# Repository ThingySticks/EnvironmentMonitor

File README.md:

# Environment Monitor ThingySticks

Particle Photon or Electron based board to measure Humidity, Temperature, Light level and pressure.

* Compaible with Particle Power Shield to allow completly wireless monitoring.
* Compaible with Particle Asset Sheild to allow location information to be included with sensor data.
* Works with Photon or Electron.

## V2:

* Temperature, Humidity (HTU21D)
* Pressure (BMP180)
* Light (TEMT6000)
* Uses a Particle Photon or Electron
* Can piggyback onto Particle Asset Tracker and other ThingySticks prototype PCBs

Available on Tindie: https://www.tindie.com/products/ThingySticks/environment-sensor-for-the-photon-or-electron/

## V3:

Uses a BME680 - These are currently very hard (i.e. impossible) to get hold of. They were expected to be sold over a year ago, hence V3 of the monitor is on-hold.

## V4:

* Total Volatile Organic Compounds (TVOC) (CCS811)
* Equivelant CO2 (CCS811)
* Temperature, Humidity and Pressure (BME280)
* Light (TEMT6000)
* Uses a Particle Photon or Electron
* Can piggyback onto Particle Asset Tracker and other ThingySticks prototype PCBs

Available on Tindie: https://www.tindie.com/products/ThingySticks/air-quality-sensor-bme280ccs811-thingystick/

Build Files
-----------

Files used by the CI server to automate Eagle as part of a build process.

Clean.bat - As it says, pre build clean.
Build.bat - The build tasks (Generate images of the schematic, PCB top, bottom, all and measurements layers).
Distribute.bat - Copy the images to the appropriate places (S3....)

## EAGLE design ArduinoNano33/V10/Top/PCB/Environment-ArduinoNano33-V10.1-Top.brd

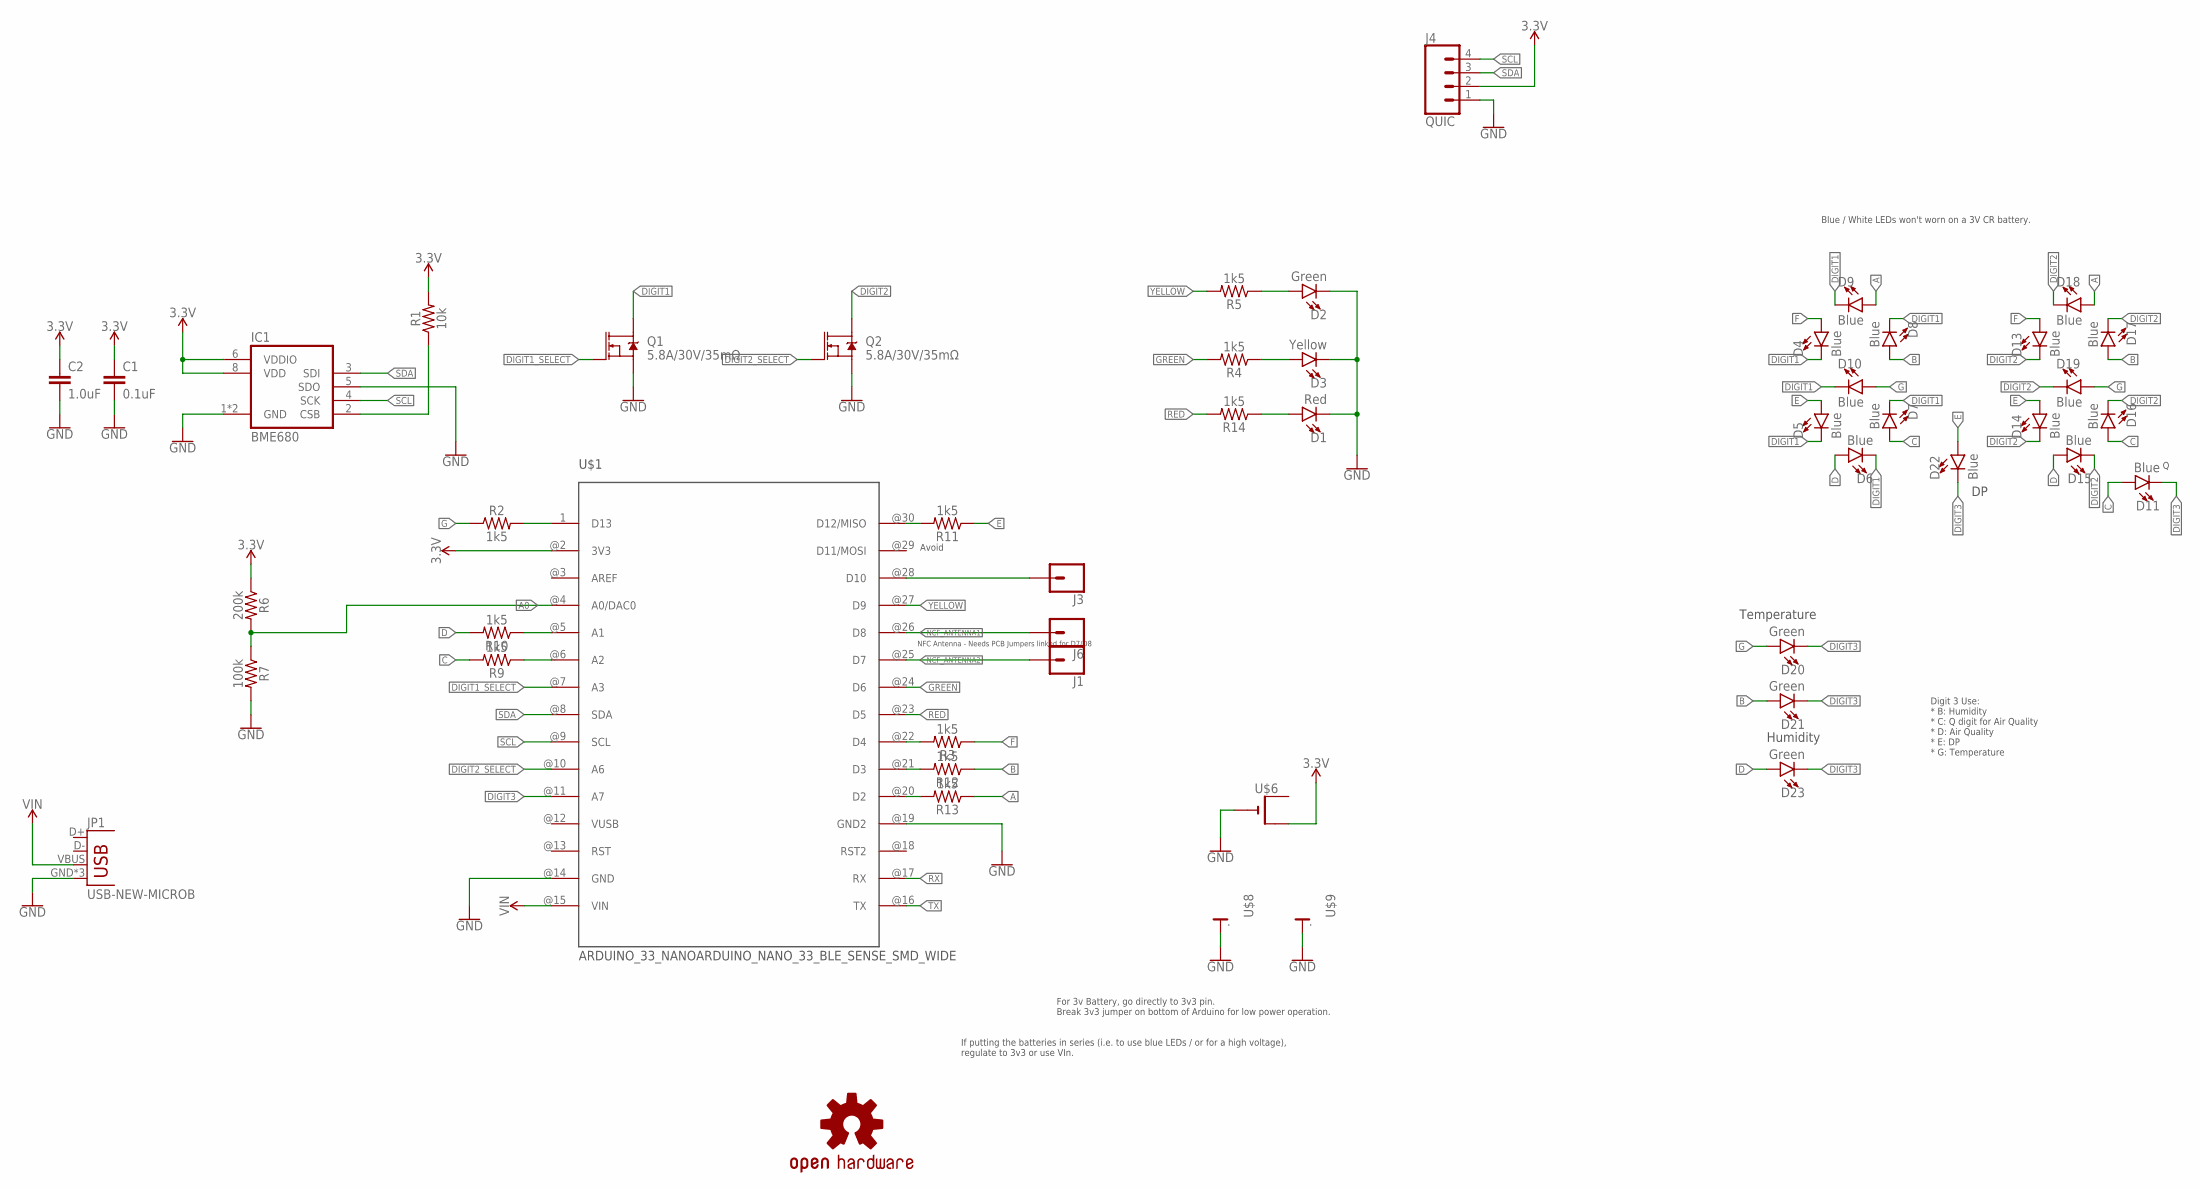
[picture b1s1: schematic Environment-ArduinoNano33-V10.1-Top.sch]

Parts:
C1: 0.1uF; 0805
C2: 1.0uF; 0805
D1: Red; LED-1206
D2, D20, D21, D23: Green; LED-1206
D3: Yellow; LED-1206
D4, D5, D6, D7, D8, D9, D10, D11, D13, D14, D15, D16, D17, D18, D19, D22: Blue; LED-1206
IC1: BME680
J1, J3, J6: CONN_01; 1X01
J4: QUIC; JST04_1MM_RA
JP1: USB-NEW-MICROB; USB-MICROB
LOGO1: OSHW-LOGOM; OSHW-LOGO-M
Q1, Q2: 5.8A/30V/35mΩ; SOT23-3
R1: 10k; 0805
R2, R3, R4, R5, R9, R10, R11, R12, R13, R14: 1k5; 0805
R6: 200k; 0805
R7: 100k; 0805
U$1: ARDUINO_33_NANOARDUINO_NANO_33_BLE_SENSE_SMD_WIDE; ARDUINO_NANO_33_SMD_WIDER_PADS
U$6: CR2032SMT; CR2032-SMD
U$8, U$9: CR2032-SPLIT-PCBCR2032-NEGATIVE; CR2032-SMD-NEGATIVE-TERMINAL

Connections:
3.3V: C1.1, C2.1, IC1.6 (VDDIO), IC1.8 (VDD), J4.2, R1.2, R6.1, U$1.@2 (3V3), U$6.+$2 (+1)
A: D9.A, D18.A, R13.1
A0: R6.2, R7.1, U$1.@4 (A0/DAC0)
B: D8.A, D17.A, D21.A, R12.1
C: D7.A, D11.A, D16.A, R9.2
D: D6.A, D15.A, D23.A, R10.2
DIGIT1: D4.C, D5.C, D6.C, D7.C, D8.C, D9.C, D10.C, Q1.3 (D)
DIGIT1_SELECT: Q1.1 (G), U$1.@7 (A3)
DIGIT2: D13.C, D14.C, D15.C, D16.C, D17.C, D18.C, D19.C, Q2.3 (D)
DIGIT2_SELECT: Q2.1 (G), U$1.@10 (A6)
DIGIT3: D11.C, D20.C, D21.C, D22.C, D23.C, U$1.@11 (A7)
E: D5.A, D14.A, D22.A, R11.1
F: D4.A, D13.A, R3.1
G: D10.A, D19.A, D20.A, R2.1
GND: C1.2, C2.2, D1.C, D2.C, D3.C, IC1.1 (GND), IC1.5 (SDO), IC1.7 (GND), J4.1, JP1.GND, JP1.MT1 (GND), JP1.MT2 (GND), Q1.2 (S), Q2.2 (S), R7.2, U$1.@14 (GND), U$1.@19 (GND2), U$6.-, U$8.-, U$9.-
GREEN: R4.2, U$1.@24 (D6)
unnamed: IC1.2 (CSB), R1.1
unnamed: D1.A, R14.1
unnamed: R9.1, U$1.@6 (A2)
unnamed: R2.2, U$1.1 (D13)
unnamed: R11.2, U$1.@30 (D12/MISO)
unnamed: R12.2, U$1.@21 (D3)
unnamed: R10.1, U$1.@5 (A1)
unnamed: R13.2, U$1.@20 (D2)
unnamed: R3.2, U$1.@22 (D4)
unnamed: D3.A, R4.1
unnamed: D2.A, R5.1
unnamed: J3.1, U$1.@28 (D10)
NCF_ANTENNA1: J6.1, U$1.@26 (D8)
NCF_ANTENNA2: J1.1, U$1.@25 (D7)
RED: R14.2, U$1.@23 (D5)
RX: U$1.@17 (RX)
SCL: IC1.4 (SCK), J4.4, U$1.@9 (SCL)
SDA: IC1.3 (SDI), J4.3, U$1.@8 (SDA)
TX: U$1.@16 (TX)
VIN: JP1.VBUS, U$1.@15 (VIN)
VUSB: U$1.@12 (VUSB)
YELLOW: R5.2, U$1.@27 (D9)

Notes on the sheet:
Temperature
Humidity
Avoid
NFC Antenna - Needs PCB Jumpers linked for D7/D8
Blue / White LEDs won't worn on a 3V CR battery.
For 3v Battery, go directly to 3v3 pin. Break 3v3 jumper on bottom of Arduino for low power operation.
If putting the batteries in series (i.e. to use blue LEDs / or for a high voltage), regulate to 3v3 or use VIn.
Digit 3 Use: * B: Humidity * C: Q digit for Air Quality * D: Air Quality * E: DP * G: Temperature

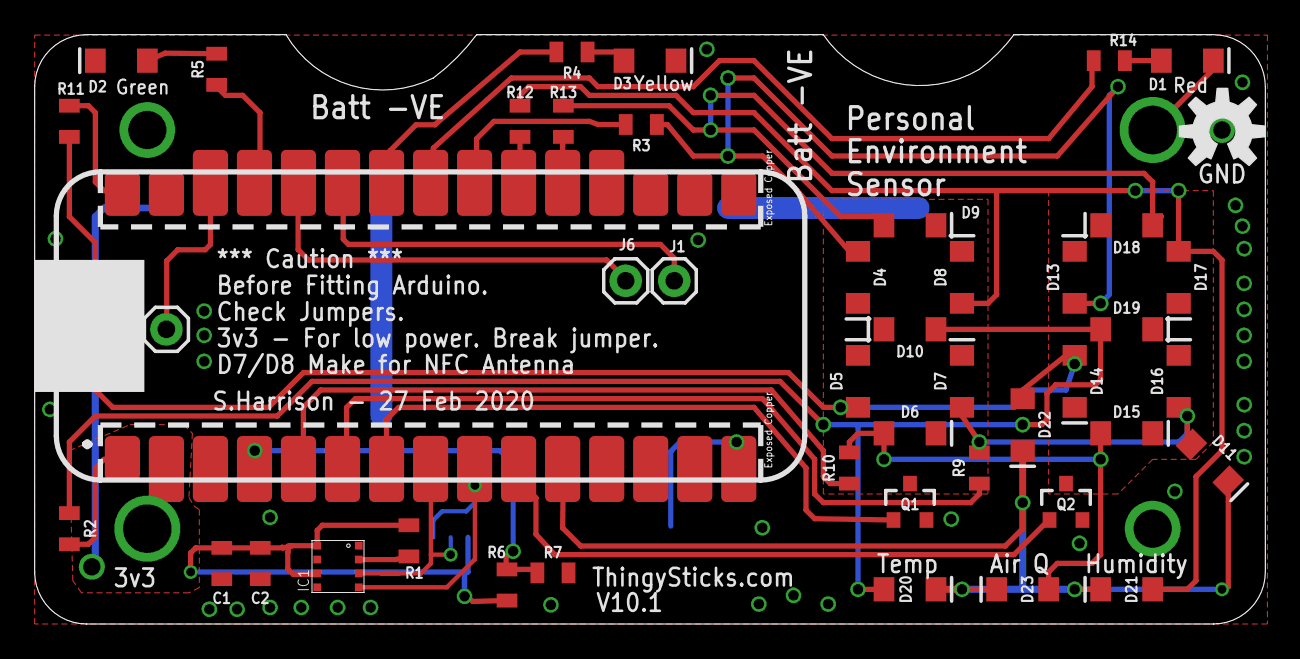
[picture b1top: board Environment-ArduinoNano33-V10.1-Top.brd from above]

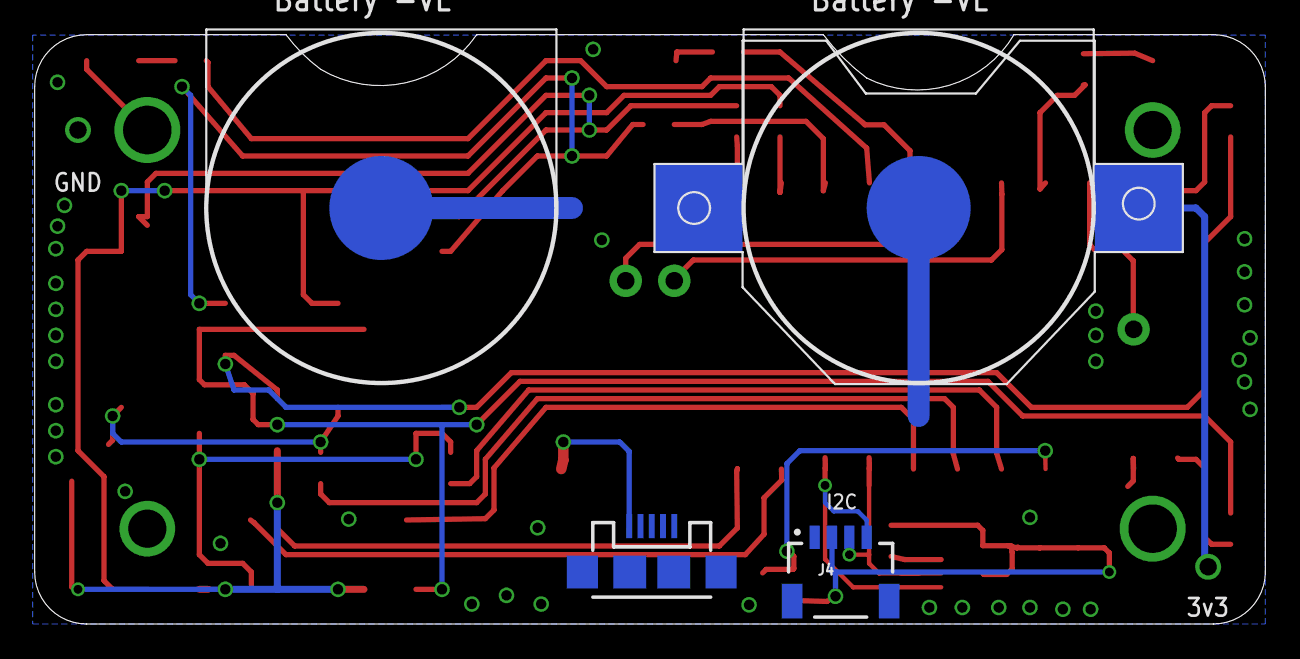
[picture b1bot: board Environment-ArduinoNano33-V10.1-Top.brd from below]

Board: 2 copper layers, 71.0 x 34.0 mm, 50 parts (5 on the bottom side), 35 nets.

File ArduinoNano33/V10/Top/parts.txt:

Partlist

Exported from Environment-ArduinoNano33-V10.1-Top.brd at 27/02/2020 07:29

EAGLE Version 7.4.0 Copyright (c) 1988-2015 CadSoft

Assembly variant: 

Part     Value                                             Package                        Library                        Position (mm)         Orientation

C1       0.1uF                                             0805                           ThingySticks                   (10.795 3.4925)       R270
C2       1.0uF                                             0805                           ThingySticks                   (13.0175 3.4925)      R270
D1       Red                                               LED-1206                       ThingySticks                   (66.5 32.5)           R0
D2       Green                                             LED-1206                       ThingySticks                   (5 32.5)              R180
D3       Yellow                                            LED-1206                       ThingySticks                   (35.5 32.5)           R0
D4       Blue                                              LED-1206                       ThingySticks                   (47.5 20)             R270
D5       Blue                                              LED-1206                       ThingySticks                   (47.5 14)             R90
D6       Blue                                              LED-1206                       ThingySticks                   (50.5 11)             R0
D7       Blue                                              LED-1206                       ThingySticks                   (53.5 14)             R90
D8       Blue                                              LED-1206                       ThingySticks                   (53.5 20)             R90
D9       Blue                                              LED-1206                       ThingySticks                   (50.5 23)             R0
D10      Blue                                              LED-1206                       ThingySticks                   (50.5 17)             R180
D11      Blue                                              LED-1206                       ThingySticks                   (67.8 9.3)            R315
D13      Blue                                              LED-1206                       ThingySticks                   (60 20)               R90
D14      Blue                                              LED-1206                       ThingySticks                   (60 14)               R270
D15      Blue                                              LED-1206                       ThingySticks                   (63 11)               R0
D16      Blue                                              LED-1206                       ThingySticks                   (66 14)               R90
D17      Blue                                              LED-1206                       ThingySticks                   (66 20)               R270
D18      Blue                                              LED-1206                       ThingySticks                   (63 23)               R180
D19      Blue                                              LED-1206                       ThingySticks                   (63 17)               R0
D20      Green                                             LED-1206                       ThingySticks                   (50.5 2)              R0
D21      Green                                             LED-1206                       ThingySticks                   (63 2)                R180
D22      Blue                                              LED-1206                       ThingySticks                   (57 11.5)             R270
D23      Green                                             LED-1206                       ThingySticks                   (57 2)                R180
IC1      BME680                                            BME680                         ThingySticks                   (17.5 3.3175)         R90
J1                                                         1X01                           SparkFun-Connectors            (36.9 19.8)           R270
J3                                                         1X01                           SparkFun-Connectors            (7.6 17)              R0
J4       QUIC                                              JST04_1MM_RA                   SparkFun-Connectors-2020-01-17 (24.5 5)              MR0
J6                                                         1X01                           SparkFun-Connectors            (34.1 19.8)           R270
JP1      USB-NEW-MICROB                                    USB-MICROB                     Tinamous                       (35.4 3)              MR0
Q1       5.8A/30V/35m?                                     SOT23-3                        SparkFun-DiscreteSemi          (50.5 7)              R0
Q2       5.8A/30V/35m?                                     SOT23-3                        SparkFun-DiscreteSemi          (59.5 7)              R0
R1       10k                                               0805                           SparkFun-Resistors             (21.59 4.7975)        R90
R2       1k5                                               0805                           SparkFun-Resistors             (2 5.5)               R270
R3       1k5                                               0805                           SparkFun-Resistors             (35 28.8175)          R180
R4       1k5                                               0805                           SparkFun-Resistors             (31 33)               R180
R5       1k5                                               0805                           SparkFun-Resistors             (10.5 32)             R270
R6       200k                                              0805                           SparkFun-Resistors             (27.25 2.25)          R90
R7       100k                                              0805                           SparkFun-Resistors             (29.9 2.95)           R0
R9       1k5                                               0805                           SparkFun-Resistors             (54.5 9)              R90
R10      1k5                                               0805                           SparkFun-Resistors             (47 9)                R90
R11      1k5                                               0805                           SparkFun-Resistors             (2 29)                R90
R12      1k5                                               0805                           SparkFun-Resistors             (28 29)               R270
R13      1k5                                               0805                           SparkFun-Resistors             (30.5 29)             R270
R14      1k5                                               0805                           SparkFun-Resistors             (62 32.5)             R180
U$1      ARDUINO_33_NANOARDUINO_NANO_33_BLE_SENSE_SMD_WIDE ARDUINO_NANO_33_SMD_WIDER_PADS ThingySticks                   (1.25 8.305)          R90
U$6                                                        CR2032-SMD                     ThingySticks                   (20 24)               MR0
U$8      CR2032-SPLIT-PCBCR2032-NEGATIVE                   CR2032-SMD-NEGATIVE-TERMINAL   ThingySticks                   (20 24)               MR0
U$9      CR2032-SPLIT-PCBCR2032-NEGATIVE                   CR2032-SMD-NEGATIVE-TERMINAL   ThingySticks                   (51 24)               MR0

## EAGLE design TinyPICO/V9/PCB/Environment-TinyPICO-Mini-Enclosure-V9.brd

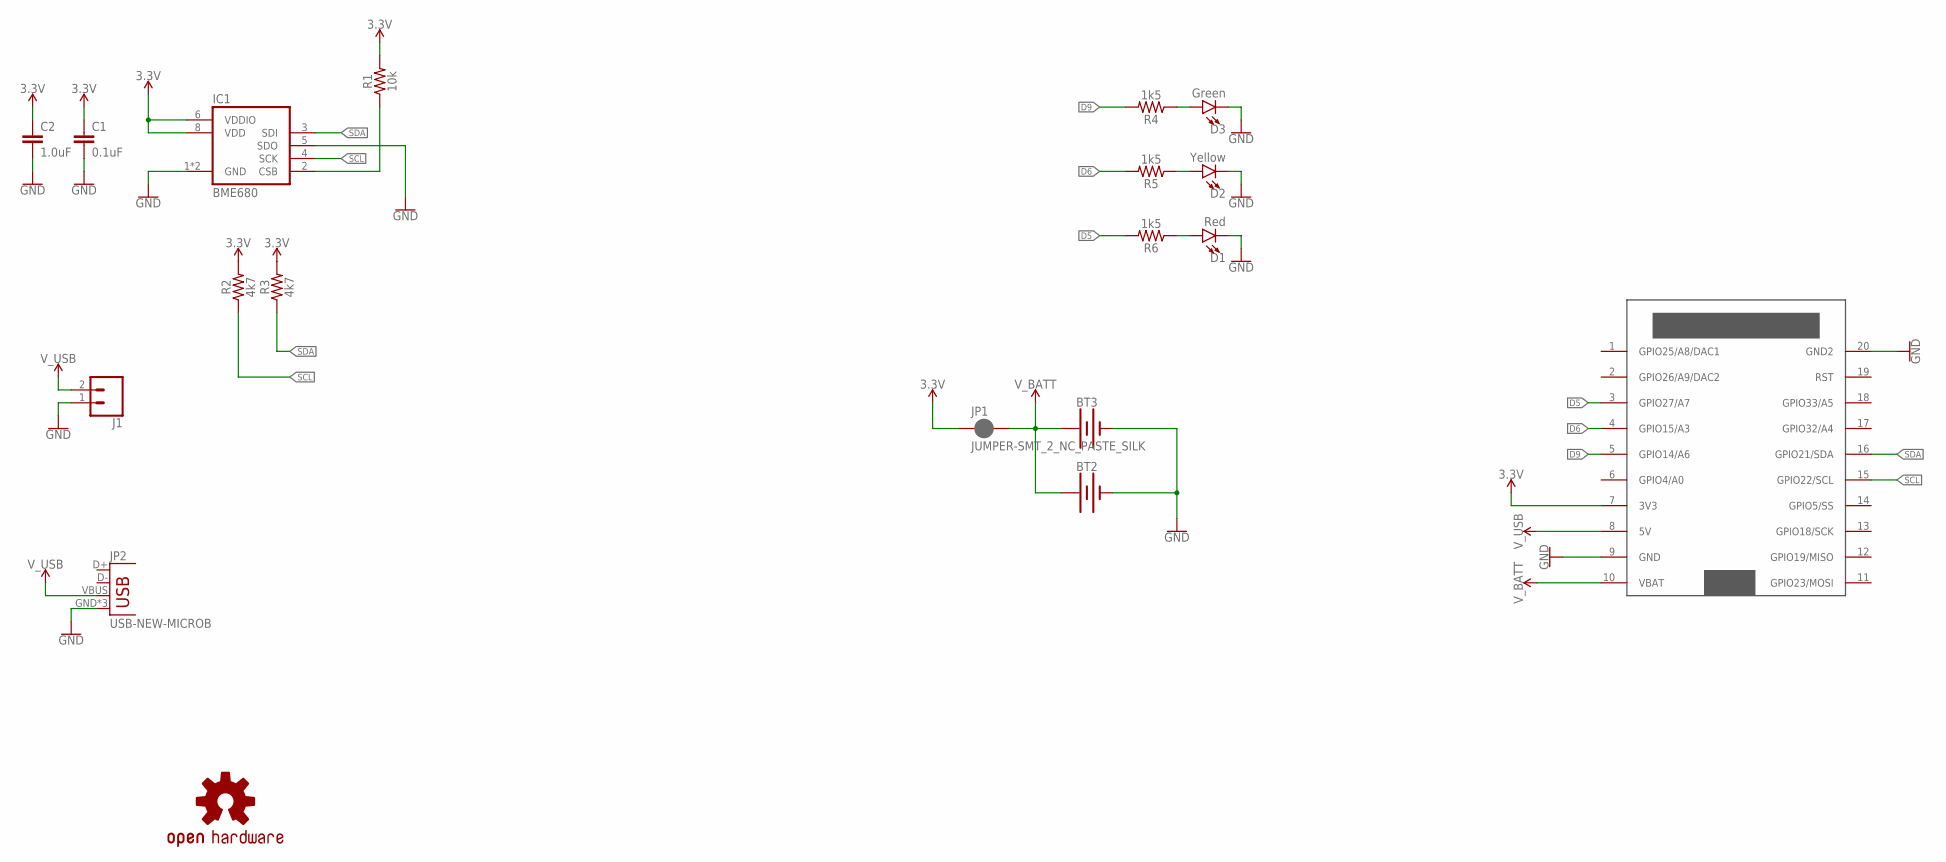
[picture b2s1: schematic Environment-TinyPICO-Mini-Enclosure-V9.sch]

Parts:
BT2, BT3: BATTERY-12MM_PTH; BATTCON_12MM_PTH
C1: 0.1uF; 0805
C2: 1.0uF; 0805
D1: Red; LED-1206
D2: Yellow; LED-1206
D3: Green; LED-1206
IC1: BME680
J1: CONN_02JST-2-PH-SIDE; JST-2-SMD
JP1: JUMPER-SMT_2_NC_PASTE_SILK; SMT-JUMPER_2_NC_PASTE_SILK
JP2: USB-NEW-MICROB; USB-MICROB
LOGO1: OSHW-LOGOM; OSHW-LOGO-M
R1: 10k; 0805
R2, R3: 4k7; 0805
R4, R5, R6: 1k5; 0805
U$2: TINY_PICO

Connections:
3.3V: C1.1, C2.1, IC1.6 (VDDIO), IC1.8 (VDD), JP1.1, R1.2, R2.2, R3.2, U$2.7 (3V3)
D5: R6.2, U$2.3 (GPIO27/A7)
D6: R5.2, U$2.4 (GPIO15/A3)
D9: R4.2, U$2.5 (GPIO14/A6)
GND: BT2.GND (-), BT3.GND (-), C1.2, C2.2, D1.C, D2.C, D3.C, IC1.1 (GND), IC1.5 (SDO), IC1.7 (GND), J1.1 (2), JP2.GND, JP2.MT1 (GND), JP2.MT2 (GND), U$2.9 (GND), U$2.20 (GND2)
unnamed: IC1.2 (CSB), R1.1
unnamed: D3.A, R4.1
unnamed: D2.A, R5.1
unnamed: D1.A, R6.1
SCL: IC1.4 (SCK), R2.1, U$2.15 (GPIO22/SCL)
SDA: IC1.3 (SDI), R3.1, U$2.16 (GPIO21/SDA)
V_BATT: BT2.VCC@1 (+), BT3.VCC@1 (+), JP1.2, U$2.10 (VBAT)
V_USB: J1.2 (1), JP2.VBUS, U$2.8 (5V)

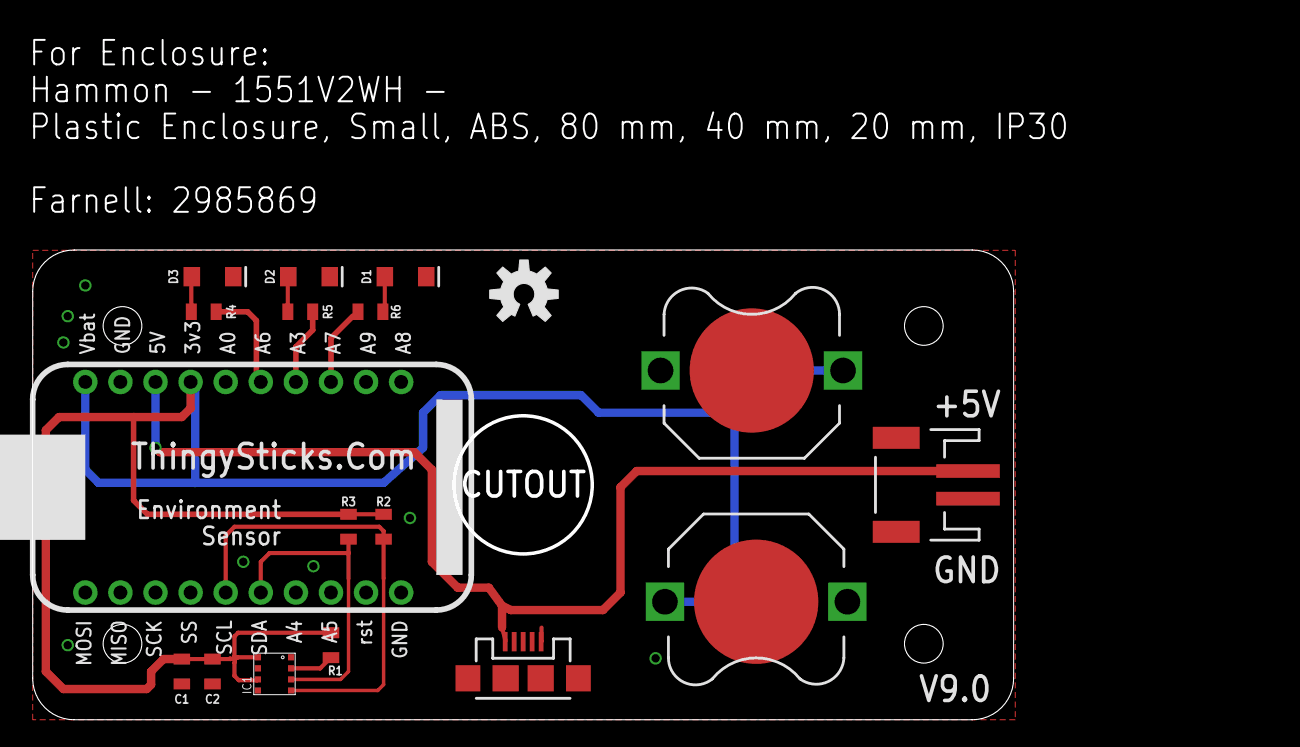
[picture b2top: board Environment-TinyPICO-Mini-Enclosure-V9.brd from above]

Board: 2 copper layers, 89.8 x 49.8 mm, 19 parts (1 on the bottom side), 13 nets.

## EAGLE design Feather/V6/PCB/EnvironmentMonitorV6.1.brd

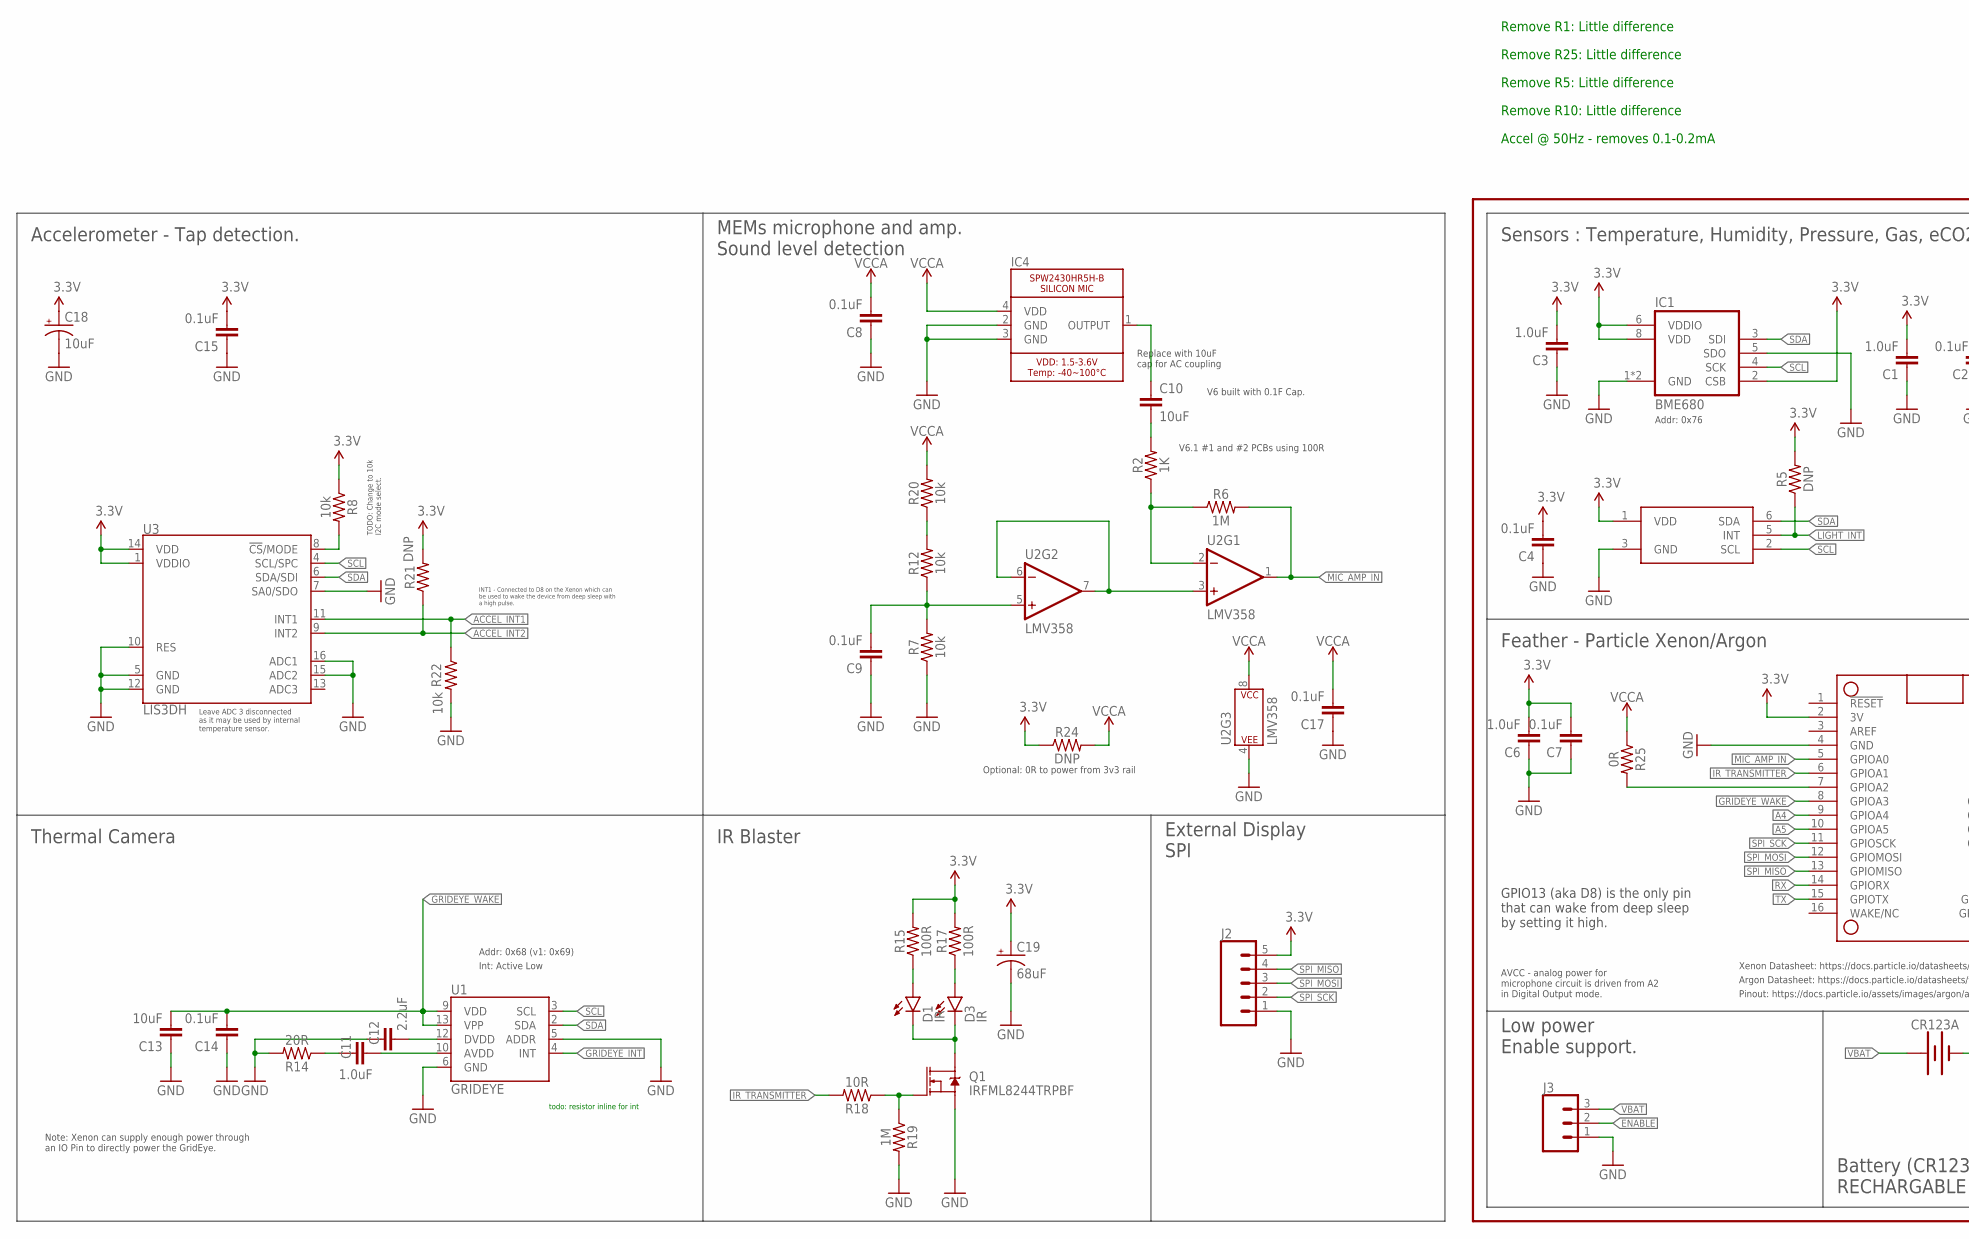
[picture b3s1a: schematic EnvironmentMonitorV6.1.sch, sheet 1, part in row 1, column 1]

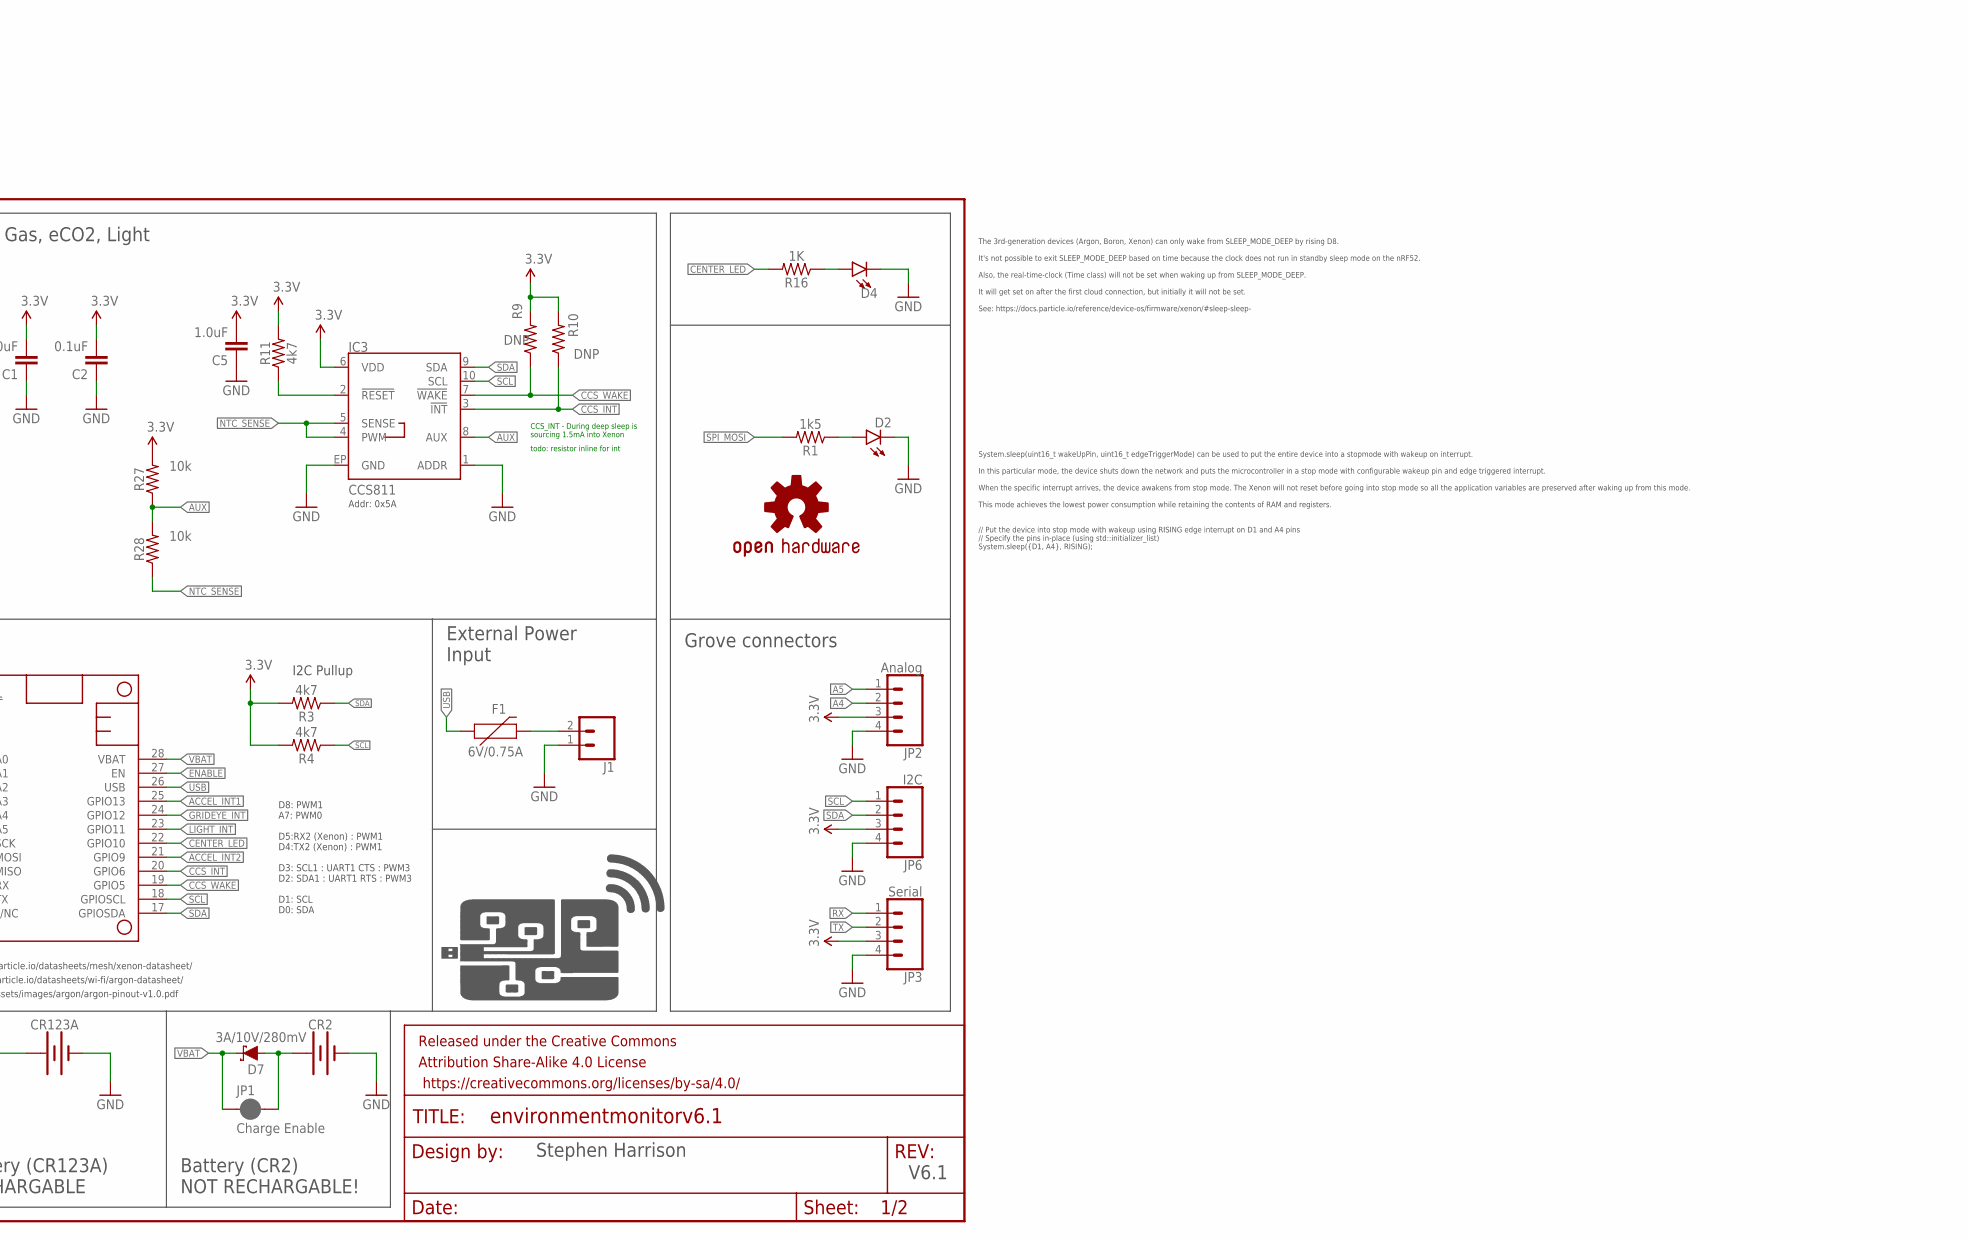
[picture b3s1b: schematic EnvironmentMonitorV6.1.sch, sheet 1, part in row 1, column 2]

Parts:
C1, C3, C5, C6, C11: 1.0uF; 0805-CAP
C2, C4, C7, C8, C9, C14, C15, C17: 0.1uF; 0805-CAP
C10, C13: 10uF; 0805-CAP
C12: 2.2uF; 0805-CAP; FARNELL 2070473
C18: 10uF; EIA3216; FARNELL 1457413
C19: 68uF; EIA3528
CR2: BATTERYCR2-NO-HOLES; BATTERY_CR2-HOLDER-NO-HOLES
CR123A: BATTERY-16340; BATTERY_16340-HOLDER
D1, D3: IR; LED-1206; FARNELL 2313501
D2: LED1206-BOTTOM; LED-1206-BOTTOM
D4: LED1206; LED-1206
D7: 3A/10V/280mV; SOD-323
F1: 6V/0.75A; 1206; FARNELL 2786571
FRAME1: FRAME-LETTER; CREATIVE_COMMONS
IC1: BME680
IC2: TCS3472; FN-6
IC3: CCS811; LGA10
IC4: SPW2430HR5H-B
IC5: FEATHERWINGPADS_AND_PLACE_ONLY; FEATHERWIND_PADS_AND_PLACE
J1: CONN_02JST-2-PH-SIDE; JST-2-SMD
J2: CONN_05SMD2; 1X05_1MM_RA
J3: CONN_03SMD; 1X03-1MM-RA
JP1: Charge Enable; SMT-JUMPER_2_NC_PASTE_SILK
JP2: Analog; JST-4-PH-GROVE
JP3: Serial; JST-4-PH-GROVE
JP6: I2C; JST-4-PH-GROVE
LOGO1: OSHW-LOGOM; OSHW-LOGO-M
Q1: IRFML8244TRPBF; SOT23-3; FARNELL 1857298
R1: 1k5; 0805
R2, R16: 1K; 0805
R3, R4, R11: 4k7; 0805
R5, R9, R10, R21, R24: DNP; 0805
R6: 1M; 0805
R7, R8, R12, R20, R22, R27, R28: 10k; 0805
R14: 20R; 0805; FARNELL 2447604
R15, R17: 100R; 0805
R18: 10R; 0805
R19: 1M; 0805; FARNELL 2129354
R25: 0R; 0805
U1: GRIDEYE; GRIDEYE-AMG88
U2: LMV358; SO08
U3: LIS3DH; LGA-16-3X3
U$1: THINGYSTICKS_LOGOLOGO_2; THINGYSTICKS_LOGO_2

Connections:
3.3V: C1.2, C2.2, C3.2, C4.2, C5.2, C6.2, C7.2, C15.2, C18.+, C19.A (+), IC1.2 (CSB), IC1.6 (VDDIO), IC1.8 (VDD), IC2.1 (VDD), IC3.6 (VDD), IC5.2 (3V), J2.5, JP2.3, JP3.3, JP6.3, R3.2, R4.2, R5.2, R8.1, R9.2, R10.2, R11.2, R15.2, R17.2, R21.2, R24.1, R27.2, U3.1 (VDDIO), U3.14 (VDD)
A4: IC5.9 (GPIOA4), JP2.2
A5: IC5.10 (GPIOA5), JP2.1
ACCEL_INT1: IC5.25 (GPIO13), R22.1, U3.11 (INT1)
ACCEL_INT2: IC5.21 (GPIO9), R21.1, U3.9 (INT2)
AUX: IC3.8 (AUX), R27.1, R28.2
CCS8_RESET: IC3.2 (!RESET!), R11.1
CCS_INT: IC3.3 (!INT!), IC5.20 (GPIO6), R10.1
CCS_WAKE: IC3.7 (!WAKE!), IC5.19 (GPIO5), R9.1
CENTER_LED: IC5.22 (GPIO10), R16.2
ENABLE: IC5.27 (EN), J3.2
GND: C1.1, C2.1, C3.1, C4.1, C5.1, C6.1, C7.1, C8.1, C9.1, C12.1, C13.1, C14.1, C15.1, C17.1, C18.-, C19.C (-), CR2.P$2 (-), CR123A.P$2 (-), D2.C, D4.C, IC1.1 (GND), IC1.5 (SDO), IC1.7 (GND), IC2.3 (GND), IC3.1 (ADDR), IC3.EP (GND), IC4.2 (GND), IC4.3 (GND), IC5.4 (GND), J1.1 (2), J2.1, J3.1, JP2.4, JP3.4, JP6.4, Q1.2 (S), R7.1, R14.2, R19.2, R22.2, U1.5 (ADDR), U1.6 (GND), U2.4 (P$V-), U3.5 (GND), U3.7 (SA0/SDO), U3.10 (RES), U3.12 (GND), U3.15 (ADC2), U3.16 (ADC1)
GRIDEYE_INT: IC5.24 (GPIO12), U1.4 (INT)
GRIDEYE_WAKE: C13.2, C14.2, IC5.8 (GPIOA3), U1.9 (VDD), U1.13 (VPP)
IR_TRANSMITTER: IC5.6 (GPIOA1), R18.2
LIGHT_INT: IC2.5 (INT), IC5.23 (GPIO11), R5.1
MIC_AMP_IN: IC5.5 (GPIOA0), R6.2, U2.1 (OUT)
unnamed: R2.1, R6.1, U2.2 (-IN)
unnamed: D1.A, R15.1
unnamed: C10.2, R2.2
unnamed: U2.3 (+IN), U2.6 (-IN), U2.7 (OUT)
unnamed: D2.A, R1.1
unnamed: C10.1, IC4.1 (OUTPUT)
unnamed: D3.A, R17.1
unnamed: C9.2, R7.2, R12.1, U2.5 (+IN)
unnamed: D1.C, D3.C, Q1.3 (D)
unnamed: R12.2, R20.1
unnamed: IC5.7 (GPIOA2), R25.2
unnamed: C12.2, U1.12 (DVDD)
unnamed: C11.2, U1.10 (AVDD)
unnamed: C11.1, R14.1
unnamed: CR2.P$1 (+), D7.A, JP1.2
unnamed: Q1.1 (G), R18.1, R19.1
unnamed: F1.2, J1.2 (1)
unnamed: D4.A, R16.1
unnamed: R8.2, U3.8 (!CS!/MODE)
NTC_SENSE: IC3.4 (PWM), IC3.5 (SENSE), R28.1
RX: IC5.14 (GPIORX), JP3.1
SCL: IC1.4 (SCK), IC2.2 (SCL), IC3.10 (SCL), IC5.18 (GPIOSCL), JP6.1, R4.1, U1.3 (SCL), U3.4 (SCL/SPC)
SDA: IC1.3 (SDI), IC2.6 (SDA), IC3.9 (SDA), IC5.17 (GPIOSDA), JP6.2, R3.1, U1.2 (SDA), U3.6 (SDA/SDI)
SPI_MISO: IC5.13 (GPIOMISO), J2.4
SPI_MOSI: IC5.12 (GPIOMOSI), J2.3, R1.2
SPI_SCK: IC5.11 (GPIOSCK), J2.2
TX: IC5.15 (GPIOTX), JP3.2
USB: F1.1, IC5.26 (USB)
VBAT: CR123A.P$1 (+), D7.C, IC5.28 (VBAT), J3.3, JP1.1
VCCA: C8.2, C17.2, IC4.4 (VDD), R20.2, R24.2, R25.1, U2.8 (P$V+)

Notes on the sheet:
I2C Pullup
V6.1
Stephen Harrison
Xenon Datasheet: https://docs.particle.io/datasheets/mesh/xenon-datasheet/
Argon Datasheet: https://docs.particle.io/datasheets/wi-fi/argon-datasheet/
Pinout: https://docs.particle.io/assets/images/argon/argon-pinout-v1.0.pdf
D8: PWM1 A7: PWM0 D5:RX2 (Xenon) : PWM1 D4:TX2 (Xenon) : PWM1 D3: SCL1 : UART1 CTS : PWM3 D2: SDA1 : UART1 RTS : PWM3 D1: SCL D0: SDA
Replace with 10uF cap for AC coupling
Addr: 0x5A
Accelerometer - Tap detection.
MEMs microphone and amp. Sound level detection
IR Blaster
Thermal Camera
Battery (CR2) NOT RECHARGABLE!
Grove connectors
Feather - Particle Xenon/Argon
Sensors : Temperature, Humidity, Pressure, Gas, eCO2, Light
External Power Input
Addr: 0x76
TODO: Change to 10k I2C mode select.
V6 built with 0.1F Cap.
Leave ADC 3 disconnected as it may be used by internal temperature sensor.
Addr: 0x68 (v1: 0x69)
Int: Active Low
AVCC - analog power for microphone circuit is driven from A2 in Digital Output mode.
GPIO13 (aka D8) is the only pin that can wake from deep sleep by setting it high.
The 3rd-generation devices (Argon, Boron, Xenon) can only wake from SLEEP_MODE_DEEP by rising D8. It's not possible to exit SLEEP_MODE_DEEP based on time because the clock does not run in standby sleep mode on the nRF52. Also, the real-time-clock (Time class) will not be set when waking up from SLE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
System.sleep(uint16_t wakeUpPin, uint16_t edgeTriggerMode) can be used to put the entire device into a stopmode with wakeup on interrupt. In this particular mode, the device shuts down the network and puts the microcontroller in a stop mode with configurable wakeup pin and edge triggered interrupt.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
// Put the device into stop mode with wakeup using RISING edge interrupt on D1 and A4 pins // Specify the pins in-place (using std::initializer_list) System.sleep({D1, A4}, RISING);
INT1 - Connected to D8 on the Xenon which can be used to wake the device from deep sleep with a high pulse.
Battery (CR123A) RECHARGABLE
Note: Xenon can supply enough power through an IO Pin to directly power the GridEye.
Low power Enable support.
Optional: 0R to power from 3v3 rail
External Display SPI
V6.1 #1 and #2 PCBs using 100R
Remove R5: Little difference
Remove R10: Little difference
Accel @ 50Hz - removes 0.1-0.2mA
Remove R25: Little difference

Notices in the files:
ArduinoNano33/V10/Firmware/PersonalEnvironmentSensor-V10.0/PersonalEnvironmentSensor-V10.0.ino:
This example code is in the public domain.
parts and their libraries:
SparkFun-Resistors: Licensing: Creative Commons ShareAlike 4.0 International - https://creativecommons.org/licenses/by-sa/4.0
SparkFun-Aesthetics: Released under the Creative Commons Attribution Share-Alike 4.0 License
SparkFun-Aesthetics: https://creativecommons.org/licenses/by-sa/4.0
